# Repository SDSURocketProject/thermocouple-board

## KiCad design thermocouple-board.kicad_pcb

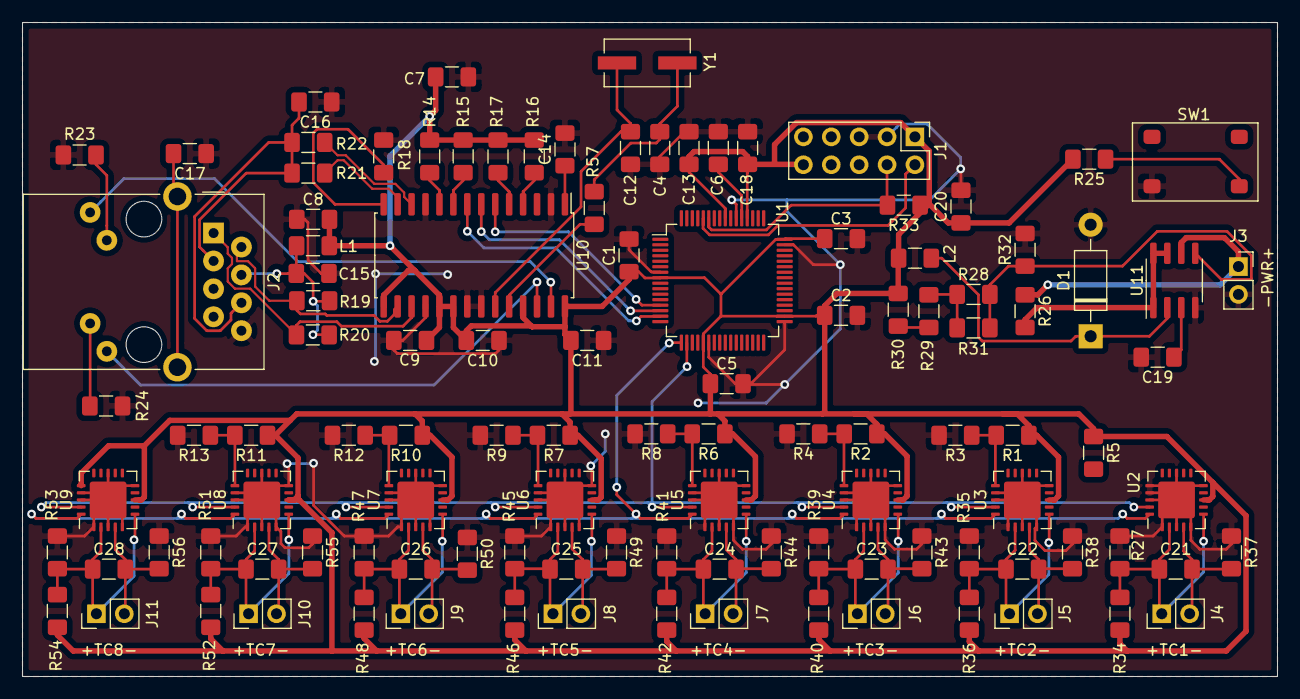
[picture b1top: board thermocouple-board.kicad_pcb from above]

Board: 2 copper layers, 114.3 x 59.6 mm, 113 parts (1 on the bottom side), 60 nets.

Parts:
C1, C2, C16: 10nF; C_1206_3216Metric_Pad1.42x1.75mm_HandSolder
C3, C4, C5, C6, C7, C15, C17, C18: 100nF; C_1206_3216Metric_Pad1.42x1.75mm_HandSolder
C8, C9, C10, C11, C12, C13: 20pF; C_1206_3216Metric_Pad1.42x1.75mm_HandSolder
C14: 10uF; C_1206_3216Metric_Pad1.42x1.75mm_HandSolder
C19: 180pF; C_1206_3216Metric_Pad1.42x1.75mm_HandSolder
C20: 100uF; C_1206_3216Metric_Pad1.42x1.75mm_HandSolder
C21, C22, C23, C24, C25, C26, C27, C28: 0.1uF; C_1206_3216Metric_Pad1.42x1.75mm_HandSolder
D1: 1N5819; D_DO-41_SOD81_P10.16mm_Horizontal
J1: Programming Header; PinHeader_2x05_P2.54mm_Vertical
J2: RJ45_Amphenol_RJMG1BD3B8K1ANR
J3: Conn_01x02; PinSocket_1x02_P2.54mm_Vertical
J4: TC1; PinHeader_1x02_P2.54mm_Vertical
J5: TC2; PinHeader_1x02_P2.54mm_Vertical
J6: TC3; PinHeader_1x02_P2.54mm_Vertical
J7: TC4; PinHeader_1x02_P2.54mm_Vertical
J8: TC5; PinHeader_1x02_P2.54mm_Vertical
J9: TC6; PinHeader_1x02_P2.54mm_Vertical
J10: TC7; PinHeader_1x02_P2.54mm_Vertical
J11: TC8; PinHeader_1x02_P2.54mm_Vertical
L1: FB/0805/600; L_1206_3216Metric_Pad1.42x1.75mm_HandSolder
L2: 47uH; L_1206_3216Metric_Pad1.42x1.75mm_HandSolder
QR*****: ID_QR_TC_PROTO_FEB_2020
R1, R2, R5, R6, R7, R10, R11, R32: 10K; R_1206_3216Metric_Pad1.42x1.75mm_HandSolder
R3: 2K2; R_1206_3216Metric_Pad1.42x1.75mm_HandSolder
R4: 4K3; R_1206_3216Metric_Pad1.42x1.75mm_HandSolder
R8: 7K5; R_1206_3216Metric_Pad1.42x1.75mm_HandSolder
R9: 13K; R_1206_3216Metric_Pad1.42x1.75mm_HandSolder
R12: 22K; R_1206_3216Metric_Pad1.42x1.75mm_HandSolder
R13: 43K; R_1206_3216Metric_Pad1.42x1.75mm_HandSolder
R14: 10k; R_1206_3216Metric_Pad1.42x1.75mm_HandSolder
R15, R16, R17: 100k; R_1206_3216Metric_Pad1.42x1.75mm_HandSolder
R18: 2R2K; R_1206_3216Metric_Pad1.42x1.75mm_HandSolder
R19, R20, R21, R22: 49R9; R_1206_3216Metric_Pad1.42x1.75mm_HandSolder
R23, R24: 220; R_1206_3216Metric_Pad1.42x1.75mm_HandSolder
R25: 330; R_1206_3216Metric_Pad1.42x1.75mm_HandSolder
R26: 0K5; R_1206_3216Metric_Pad1.42x1.75mm_HandSolder
R27, R35, R37, R38, R39, R41, R43, R44, R45, R47, R49, R50, R51, R53, R55, R56: 2M; R_1206_3216Metric_Pad1.42x1.75mm_HandSolder
R28, R31: 27K; R_1206_3216Metric_Pad1.42x1.75mm_HandSolder
R29: 820; R_1206_3216Metric_Pad1.42x1.75mm_HandSolder
R30: 470; R_1206_3216Metric_Pad1.42x1.75mm_HandSolder
R33: 1K; R_1206_3216Metric_Pad1.42x1.75mm_HandSolder
R34, R36, R40, R42, R46, R48, R52, R54: 1M; R_1206_3216Metric_Pad1.42x1.75mm_HandSolder
R57: 5M; R_1206_3216Metric_Pad1.42x1.75mm_HandSolder
SW1: RESET; omron-b3s
U1: ATSAME51J20A-A; TQFP-64_10x10mm_P0.5mm
U2, U3, U4, U5, U6, U7, U8, U9: MCP9601_ZM; QFN-20-1EP_5x5mm_P0.65mm_EP3.35x3.35mm
U10: ENC28J60x-SO; SOIC-28W_7.5x17.9mm_P1.27mm
U11: MC33063AD; SOIC-8_3.9x4.9mm_P1.27mm
Y1: 25MHz; Crystal_SMD_ECS_CSM3X-2Pin_7.6x4.1mm

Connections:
+3V3: C1.1, C2.1, C3.1, C4.1, C5.1, C7.2, C8.2, C9.2, C10.2, C11.2, C18.1, C20.1, J1.1, J1.10, L1.1, L2.2, R1.1, R2.1, R5.1, R6.1, R7.1, R10.1, R11.1, R14.2, R15.2, R16.2, R17.2, R25.2, R30.1, R33.1, R34.2, R36.2, R40.2, R42.2, R46.2, R48.2, R52.2, R54.2, U1.8, U1.21, U1.34, U1.48, U1.52, U1.56, U2.8, U3.8, U4.8, U5.8, U6.8, U7.8, U8.8, U9.8, U9.16, U10.15, U10.19, U10.20, U10.25, U10.28
/Ethernet/LEDA: J2.L4, U10.27
/Ethernet/LEDB: J2.L1, U10.26
/Ethernet/MISO: U1.13, U10.6
/Ethernet/MOSI: U1.14, U10.7
/Ethernet/SCK: U1.15, U10.8
/Ethernet/TPIN+: R21.1, U10.13
/Ethernet/TPIN-: R22.1, U10.12
/Ethernet/TPOUT+: J2.R1, R20.2, U10.17
/Ethernet/TPOUT-: J2.R2, R19.2, U10.16
/MCU/SWCLK: J1.4, R33.2, U1.59
/MCU/SWDIO: J1.2, U1.60
/Thermocouples/ADDR_2: R1.2, R3.1, U3.16
/Thermocouples/ADDR_3: R2.2, R4.1, U4.16
/Thermocouples/ADDR_4: R6.2, R8.1, U5.16
/Thermocouples/ADDR_5: R7.2, R9.1, U6.16
/Thermocouples/ADDR_6: R10.2, R12.1, U7.16
/Thermocouples/ADDR_7: R11.2, R13.1, U8.16
/Thermocouples/SCL: U1.18, U2.19, U3.19, U4.19, U5.19, U6.19, U7.19, U8.19, U9.19
/Thermocouples/SDA: U1.17, U2.20, U3.20, U4.20, U5.20, U6.20, U7.20, U8.20, U9.20
/Thermocouples/TC1+: C21.1, J4.1, R27.2, R34.1, U2.2, U2.6
/Thermocouples/TC1-: C21.2, J4.2, R37.2, U2.4
/Thermocouples/TC2+: C22.1, J5.1, R35.2, R36.1, U3.2, U3.6
/Thermocouples/TC2-: C22.2, J5.2, R38.2, U3.4
/Thermocouples/TC3+: C23.1, J6.1, R39.2, R40.1, U4.2, U4.6
/Thermocouples/TC3-: C23.2, J6.2, R43.2, U4.4
/Thermocouples/TC4+: C24.1, J7.1, R41.2, R42.1, U5.2, U5.6
/Thermocouples/TC4-: C24.2, J7.2, R44.2, U5.4
/Thermocouples/TC5+: C25.1, J8.1, R45.2, R46.1, U6.2, U6.6
/Thermocouples/TC5-: C25.2, J8.2, R49.2, U6.4
/Thermocouples/TC6+: C26.1, J9.1, R47.2, R48.1, U7.2, U7.6
/Thermocouples/TC6-: C26.2, J9.2, R50.2, U7.4
/Thermocouples/TC7+: C27.1, J10.1, R51.2, R52.1, U8.2, U8.6
/Thermocouples/TC7-: C27.2, J10.2, R55.2, U8.4
/Thermocouples/TC8+: C28.1, J11.1, R53.2, R54.1, U9.2, U9.6
/Thermocouples/TC8-: C28.2, J11.2, R56.2, U9.4
GND: C1.2, C2.2, C3.2, C4.2, C5.2, C6.2, C7.1, C8.1, C9.1, C10.1, C11.1, C12.2, C13.2, C14.2, C15.1, C16.1, C17.1, C18.2, C19.2, C20.2, D1.2, J1.3, J1.5, J2.R8, J3.2, R3.2, R4.2, R8.2, R9.2, R12.2, R13.2, R18.2, R23.2, R24.2, R27.1, R32.2, R35.1, R37.1, R38.1, R39.1, R41.1, R43.1, R44.1, R45.1, R47.1, R49.1, R50.1, R51.1, R53.1, R55.1, R56.1, SW1.2, U1.7, U1.22, U1.33, U1.47, U1.54, U2.1, U2.3, U2.5, U2.10, U2.13, U2.16, U2.17, U2.18, U2.21, U3.1, U3.3, U3.5, U3.10, U3.13, U3.17, U3.18, U3.21, U4.1, U4.3, U4.5, U4.10, U4.13, U4.17, U4.18, U4.21, U5.1, U5.3, U5.5, U5.10, U5.13, U5.17, U5.18, U5.21, U6.1, U6.3, U6.5, U6.10, U6.13, U6.17, U6.18, U6.21, U7.1, U7.3, U7.5, U7.10, U7.13, U7.17, U7.18, U7.21, U8.1, U8.3, U8.5, U8.10, U8.13, U8.17, U8.18, U8.21, U9.1, U9.3, U9.5, U9.10, U9.13, U9.17, U9.18, U9.21, U10.2, U10.11, U10.18, U10.21, U10.22, U11.4
unnamed: C6.1, U1.53
unnamed: C12.1, U10.23, Y1.1
unnamed: C13.1, R57.2, Y1.2
unnamed: C14.1, U10.1
unnamed: C15.2, J2.R4, L1.2, R19.1, R20.1
unnamed: C16.2, J2.R3, J2.R6, R21.2, R22.2
unnamed: C17.2, J2.13
unnamed: C19.1, U11.3
unnamed: D1.1, L2.1, U11.2
unnamed: J2.L2, R24.1
unnamed: J2.L3, R23.1
unnamed: R14.1, U10.10
unnamed: R15.1, U10.9
unnamed: R16.1, U10.4
unnamed: R17.1, U10.5
unnamed: R18.1, U10.14
unnamed: R25.1, SW1.1
unnamed: R26.2, U11.1, U11.7, U11.8
unnamed: R28.1, R29.2, R31.1
unnamed: R28.2, R31.2, R32.1, U11.5
unnamed: R29.1, R30.2
unnamed: R57.1, U10.24
VCC: J3.1, R26.1, U11.6

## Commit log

2020-01-02 Add empty KiCad project
2020-01-02 Add datasheets for currently used ICs
    - MCP9600 Thermocouple Conditioning IC
    - ATMEGA328PB 8-bit Microcontroller
    - ENC28J60 - PHY/MAC Ethernet Controller
2020-01-06 Add first attempt at MCU and MAC/PHY schematics
    MCU is standard ATMEAG328PB with SPI connection to the ENC28J60 Ethernet
    PHY/MAC controller and an ICSP header for programming. The ATMEGA328PB
    was chosen because it is a familiar platform for Arduino users, with
    additional serial interfaces to what the ATMEGA328P has.
    Wiring of the ENC28J60 is based on the schematic of the MOD-ENC28J60
    Ethernet Development Board from Olimex.
2020-01-06 Import gitignore from avionics/helix-hardware
2020-01-06 Revise schematic based on sanity check from David
    - Replace global net labels with local net labels
    - Add missing SPI net labels to U2
    - Reorient GND ports to face down and +5V/+3V3 ports to face up
    - Properly ground shield pin on J2
2020-02-16 Add prototype thermocouple schematic
2020-02-17 Replace MCU with more effective alternative
    The ATMEGA328PB raised concerns about its ability to process input data
    at an acceptable speed, and so it has beed replaced with the
    ATSAME51J20A, the same MCU used in the Helix expansion boards. This will
    also increase cross-compatibility with components and will decrease the
    number of unique components used in Avionics.
2020-02-18 Rename to thermocouple-board
2020-02-18 Add footprints and create PCB file
2020-02-20 Begin PCB placement and routing
2020-02-20 Add PDF schematics
2020-02-22 Update schematic for MCP9601 circuit alerts
    Added the required circuitry to support the Open-circuit and
    Short-circuit detection functionality of the MCP9601, as per figure 1-1
    in the datasheet.
2020-02-22 Preliminary replacement of components for MCP9601
    Following the changes in the previous commit, all components have been
    replaced in a bid for more space efficiency to reduce costs.
    No traces have been laid at this point.
2020-02-22 Complete routing for PCB traces
2020-02-22 Replace capacitor footprints with 1206
